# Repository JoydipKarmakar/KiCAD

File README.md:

# KiCAD
Collection of KiCad projects, footprints, and schematic libraries for hardware design.

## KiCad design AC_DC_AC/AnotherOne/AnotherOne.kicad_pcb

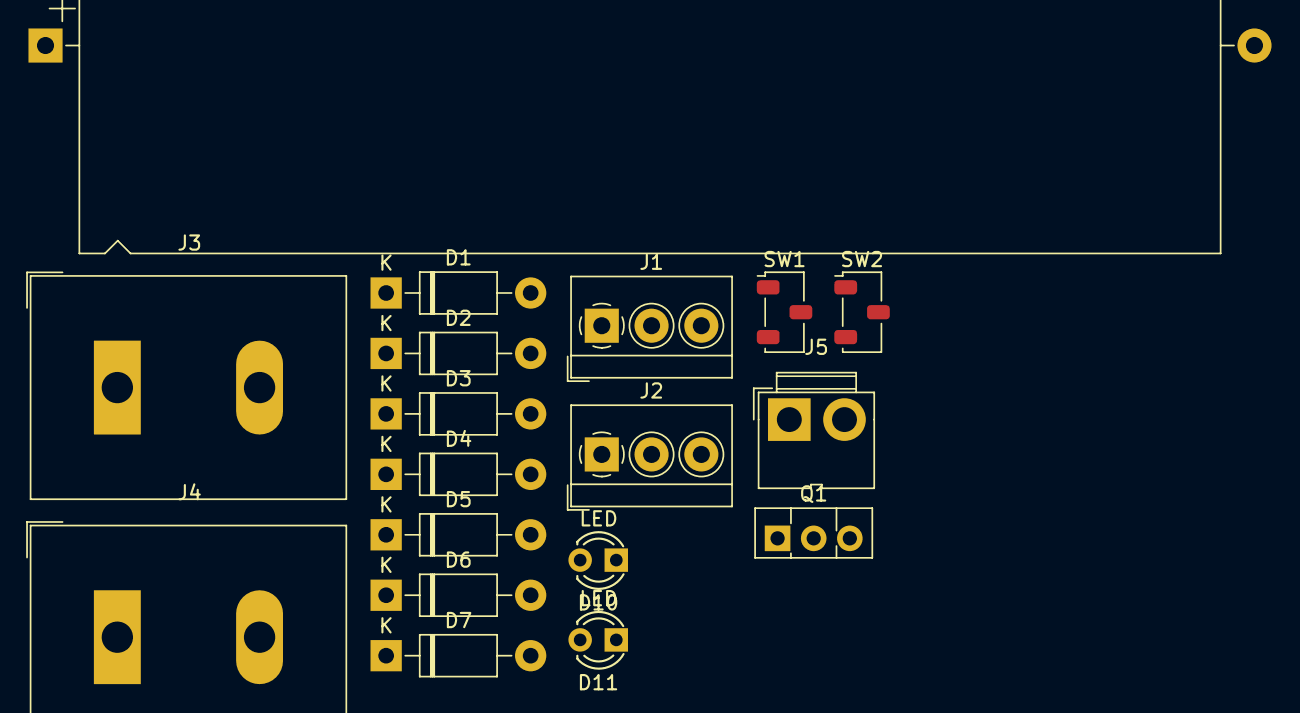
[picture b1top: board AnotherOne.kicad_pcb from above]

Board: 2 copper layers, 18 parts (0 on the bottom side), 6 nets, no tracks yet.

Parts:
C4: C_Polarized; CP_Axial_L80.0mm_D29.0mm_P85.00mm_Horizontal
D1, D2, D3, D4, D5, D6, D7: 1N4007; D_DO-41_SOD81_P10.16mm_Horizontal
D10, D11: LED; LED_3mm_C1A2
J1, J2: Screw_Terminal_01x03; TerminalBlock_4Ucon_1x03_P3.50mm_Horizontal
J3, J4: Screw_Terminal_01x02; TerminalBlock_Dinkle_DT-55-B01X-02_P10.00mm
J5: Conn_01x02_Pin; JWT_A3963_1x02_P3.96mm_Vertical
Q1: 2SB631; TO-126-3_Vertical
SW1, SW2: SW_Nidec_CAS-120A1; Nidec_Copal_CAS-120A

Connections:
unnamed: D5.2 (A), J5.1, SW1.2 (B)
unnamed: D4.1 (K), D6.2 (A)
unnamed: D7.2 (A), J3.1
unnamed: D7.1 (K), J1.1, J5.2
unnamed: Q1.3 (B), SW2.2 (B)
unnamed: D11.1 (K), J3.2

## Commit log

2025-08-19 Added New Files
2025-08-19 all files added
2025-09-14 AC to DC to HVDC converter
2025-09-14 AC_DC_HVDC
2025-09-17 all files are arranged
